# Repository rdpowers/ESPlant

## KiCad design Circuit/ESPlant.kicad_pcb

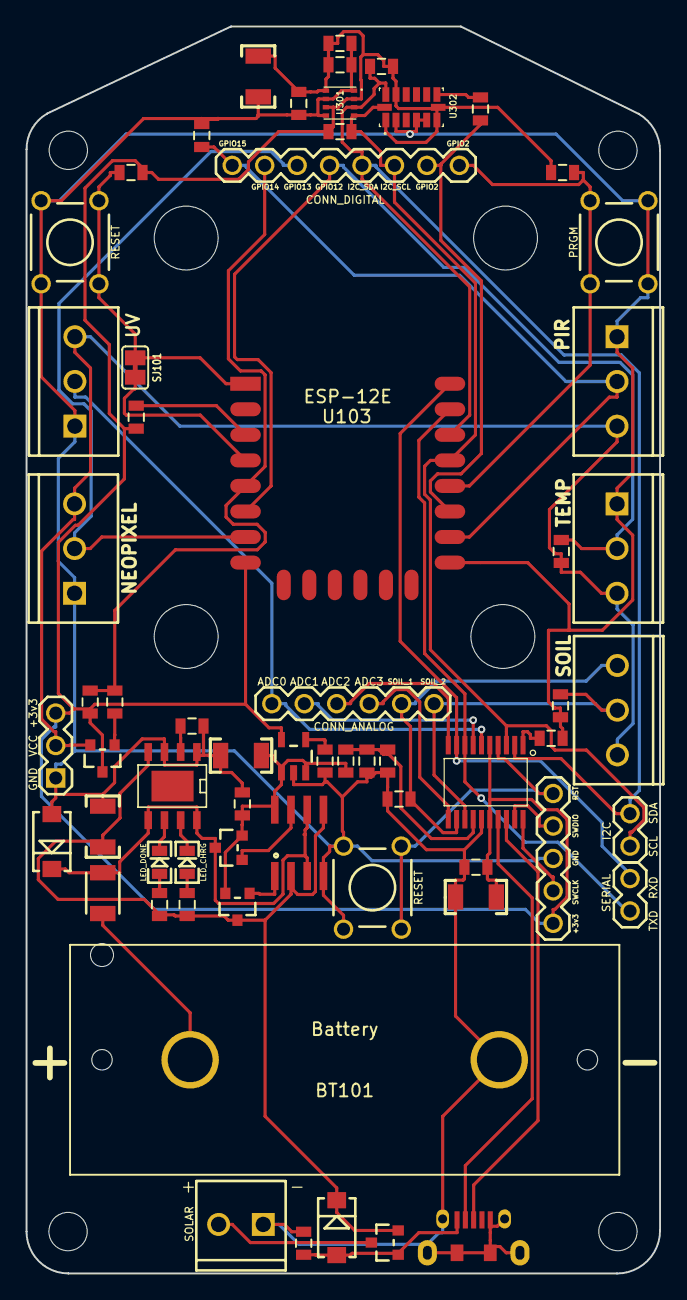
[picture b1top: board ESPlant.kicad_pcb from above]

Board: 2 copper layers, 49.6 x 97.6 mm, 72 parts (0 on the bottom side), 45 nets.

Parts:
BT101: Battery; CR123_Holder
C101, C104, C202: 100nF; 0805
C102, C107: 100nF 6.3V; 0805
C103, C201: 10uF 16V; 1210_CAP
C106, C203: 220uF 16V; 1210_CAP
C301, C302: 1uF 6.3V; 0805
D101, D201: SS14; DIODE_SMA
F101: 1A PTC; 1210
LED201: LED_DONE; LED-0805
LED202: LED_CHRG; LED-0805
P1: SOIL; SCREWTERMINAL-3.5MM-3
P101: CONN_DIGITAL; 1X08
P102: CONN_ANALOG; 1X06
P103: SERIAL; 1X02
P104: I2C; 1X02
P105: SOLAR; SCREWTERMINAL-3.5MM-2
P106: USB_5PIN_SHELL; USB-MICRO-5pin_PTHMOUNT
P109: PWR; 1X03
P110: STM_PGM; 1X05
P111: UV; SCREWTERMINAL-3.5MM-3
P112: TEMP; SCREWTERMINAL-3.5MM-3
P113: NEOPIXEL; SCREWTERMINAL-3.5MM-3
P114: PIR; SCREWTERMINAL-3.5MM-3
Q101, Q201, Q202, Q203: FDN340P; SOT23_FET
R101: 10K DNP; 0805
R102, R103: 100K; 0805
R104, R105, R109, R111, R112, R113: 10K; 0805
R106, R201: 1K; 0805
R107: 56K 1%; 0805
R108: 47K 1%; 0805
R110: 4.7K DNP; 0805
R202, R203: 330R; 0805
R204: 8.2K; 0805
R301, R302: 4.7K; 0805
REF01, REF02, REF03, REF04: MOUNT; MountingHole_5mm
REF05, REF06, REF07, REF08: MOUNT; MountingHole_3mm
REG101: SPX3819M5; SOT23-5
SJ101: SJ; SJ_SHORTED
SW101, SW103: RESET; SW_PUSHBUTTON_PTH
SW102: PRGM; SW_PUSHBUTTON_PTH
U101: STM32F042F; TSSOP20_4mm
U103: ESP-12E
U201: CN3063; CN3063_SOIC8_EP
U202: MCP6002; SO08_4mm
U301: BME280
U302: ADXL345

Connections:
+3V3: C102.1, C103.1, C106.1, C107.1, C301.1, C302.1, P109.1, P110.1, Q101.D, R104.1, R111.2, R112.2, R113.1, R301.1, R302.1, REG101.5, U101.5, U101.16, U103.8, U301.2, U301.6, U301.8, U302.1, U302.6, U302.7, U302.12
/ADC0: P102.1, P111.2, U101.6
/ADC1: P102.2, U101.7
/ADC2: P102.3, U101.10
/ADC3: P102.4, U101.11
/BAT+: BT101.1, F101.1
/ESP_EN: R113.2, U103.3
/ESP_~RESET: R111.1, SJ101.1, SW101.2, U103.1
/GPIO0: P101.1, R112.1, SW102.2, U103.18
/GPIO2: P101.2, R105.1, U103.17
/GPIO12: P101.5, P112.2, R110.2, U103.6
/GPIO13: P101.6, P113.2, U103.7
/GPIO14: P101.7, R104.2, R106.2, U103.5
/GPIO15: P101.8, P114.2, R109.1, U103.16
/GPIO16: SJ101.2, U103.4
/I2C Sensors/ADXL_INT: R105.2, U302.8
/I2C Sensors/I2C_SCL: P101.3, P104.1, R302.2, U101.3, U103.19, U301.4, U302.14
/I2C Sensors/I2C_SDA: P101.4, P104.2, R301.2, U101.2, U103.20, U301.3, U302.13
/Power/GBAT: Q203.G, U202.7
/Power/GIN: Q202.G, U202.1
/Power/SOLAR_IN: P105.1, Q201.D
/Power/USB_IN: D201.A, P106.1, Q201.G, R201.1
/Power/VBAT: D101.K, F101.2, Q203.D, U201.5, U201.8, U202.3, U202.6
/Power/VIN: C201.1, D201.K, Q201.S, Q202.D, R202.1, R203.1, U201.4, U202.2, U202.5
/Power/VOUT: C202.1, C203.2, Q202.S, Q203.S, R107.1, REG101.1, REG101.3, U202.8
/Power/~CHRG: LED202.K, U201.7
/Power/~DONE: LED201.K, U201.6
/SOIL_1: P1.3, P102.5, R102.1, U101.12
/SOIL_2: P1.2, P102.6, R103.1, U101.13
/STM_BOOT: R101.1, U101.1
/STM_RXD: P103.1, U101.9, U103.22
/STM_SWCLK: P110.2, U101.20
/STM_SWDIO: P110.4, U101.19
/STM_TXD: P103.2, U101.8, U103.21
/STM_~RESET: P110.5, SW103.2, U101.4
/USB_D+: P106.3, U101.18
/USB_D-: P106.2, U101.17
/VCC_SENS: P1.1, P109.2, P111.1, P112.1, P113.1, P114.1, Q101.S, R110.1
GND: BT101.2, C101.2, C102.2, C103.2, C104.2, C106.2, C107.2, C201.2, C202.2, C203.1, C301.2, C302.2, D101.A, P105.2, P106.5, P106.SHLD, P109.3, P110.3, P111.3, P112.3, P113.3, P114.3, R101.2, R102.2, R103.2, R108.2, R109.2, R201.2, R204.2, REG101.2, SW101.1, SW102.1, SW103.1, U101.15, U103.15, U201.1, U201.3, U202.4, U301.1, U301.5, U301.7, U302.2, U302.4, U302.5
unnamed: C101.1, REG101.4
unnamed: C104.1, R107.2, R108.1, U101.14
unnamed: LED201.A, R202.2
unnamed: LED202.A, R203.2
unnamed: Q101.G, R106.1
unnamed: R204.1, U201.2

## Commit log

2015-11-28 10x5 PCB design.
2015-11-29 5 Vias, no text.
2015-11-29 Traces in.
2015-11-29 Added text.
2015-11-29 Fixed Readme
2015-12-04 Adding photo of actual boards.
2015-12-04 Updated the silkscreen text
2015-12-10 Updates to silkscreen.
